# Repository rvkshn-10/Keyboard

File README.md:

# Keyboard 
Hello, this is a Keyboard Project which was my first time developing a PCB, after numerous errors and attempts, I finally got it done thanks to the Half Life Program at Hack Club. 
Firmware for the Raspberry Pi Pico is in the firmware folder, while the PCB and schematic files are in the main folder. Inside of the keyboard61 folder you can find the fabrication files for the circuit board. The layout and pictures have also been put there.

## Bill of materials

This table lists the whole planned build and who is responsible for each purchase. The Hack Club request covers only the rows marked **Hack Club funding request**, the other parts are planned personal purchases. Prices are estimates in USD before checkout unless noted. The PCB estimate is from the older, larger outline and needs a new quote for the compact layout.

| Part | Qty | Unit | Total | Vendor | Buyer |
| --- | ---: | ---: | ---: | --- | --- |
| [Keyboard PCB, batch of 5](https://cart.jlcpcb.com/quote) | 1 | $31.15 | $31.15 | JLCPCB | Hack Club funding request; re-quote revised board |
| [onsemi 1N4148 DO-35 diodes](https://www.digikey.com/en/products/detail/onsemi/1N4148/458603) | 61 | $0.0422 | $2.57 | DigiKey | Hack Club funding request |
| [Raspberry Pi Pico H](https://www.digikey.com/en/products/detail/raspberry-pi/SC0917/16608257) | 1 | $5.00 | $5.00 | DigiKey | Hack Club funding request |
| [Adafruit Pico female socket pair](https://www.digikey.com/en/products/detail/adafruit-industries-llc/5583/16688063) | 1 pair | $0.95 | $0.95 | DigiKey | Hack Club funding request |
| [Adafruit 4111 USB-A to Micro-B cable, 1 m](https://www.digikey.com/en/products/detail/adafruit-industries-llc/4111/9992197) | 1 | $3.95 | $3.95 | DigiKey | Hack Club funding request |
| **Hack Club request parts subtotal** |  |  | **$43.62** |  |  |
| Tax and shipping estimate (not a current checkout quote) | 1 | $20.00 | $20.00 | Multiple vendors | Hack Club request estimate |
| **Estimated Hack Club total** |  |  | **$63.62 of $65** |  | **$1.38 remaining; confirm current carts** |
| [Gateron Milky Yellow Pro V2, 70 switches](https://www.amazon.com/dp/B0BBPPP7HD) | 1 pack | $19.99 | $19.99 | Amazon | Personal purchase |
| [XVX green keycap set](https://www.amazon.com/dp/B0DNMV32L2) | 1 set | $13.99 | $13.99 | Amazon | Personal purchase |
| [Chilkey snap-in stabilizer kit](https://www.amazon.com/dp/B0D2KMVVL3) | 1 kit | $21.99 | $21.99 | Amazon | Personal purchase |
| [Tactile reset buttons, 126-piece pack](https://www.amazon.com/dp/B0D5M2ZNSL) | 1 pack | $4.66 | $4.66 | Amazon | Personal purchase |
| [M3 nylon standoff and fastener kit](https://www.amazon.com/dp/B0G3XCGSNV) | 1 kit | $6.99 | $6.99 | Amazon | Personal purchase |
| [Adafruit rotary encoder with knob](https://www.adafruit.com/product/377) | 1 | $4.50 | $4.50 | Adafruit | Personal purchase |
| [Adafruit 1955 jumper wire pack](https://www.adafruit.com/product/1955) | 1 pack | $3.95 | $3.95 | Adafruit | Personal purchase |
| [ShillehTek AA317 2.8-inch ILI9341 TFT](https://shillehtek.com/products/2-8-spi-tft-lcd-touch-screen-module-240x320-ili9341-for-arduino) | 1 | $10.99 | $10.99 | ShillehTek | Personal purchase |
| Paid printing service for case, plate, and spacers | 1 | Quote needed | Quote needed | TBD | Personal purchase; quote current CAD |
| **Personal parts subtotal** |  |  | **$87.06** |  | **Before tax, shipping, and printing** |
| **Combined known parts subtotal** |  |  | **$130.68** |  | **Before tax, shipping, and printing** |

The $20 tax-and-shipping amount is a planning placeholder, not a confirmed cart total. The Amazon prices were last checked October 7, 2026 and need checkout verification. The prior enclosure-print quote used older geometry and is not included.

## Compact PCB layout

The current KiCad board outline is 295.05 × 100.05 mm, reduced from the earlier 295 × 168 mm layout. The Pico is mounted on the underside beneath the left key area, so it does not need a separate blank strip above the keyboard. Moving it beside the full-width key matrix would require a wider board or a separate wired module, so the current compact outline keeps it inside the keyboard footprint. The two KiCad 3D renders below show the front and underside, physical clearance still needs a hardware fit check.

Here are some images of my work!

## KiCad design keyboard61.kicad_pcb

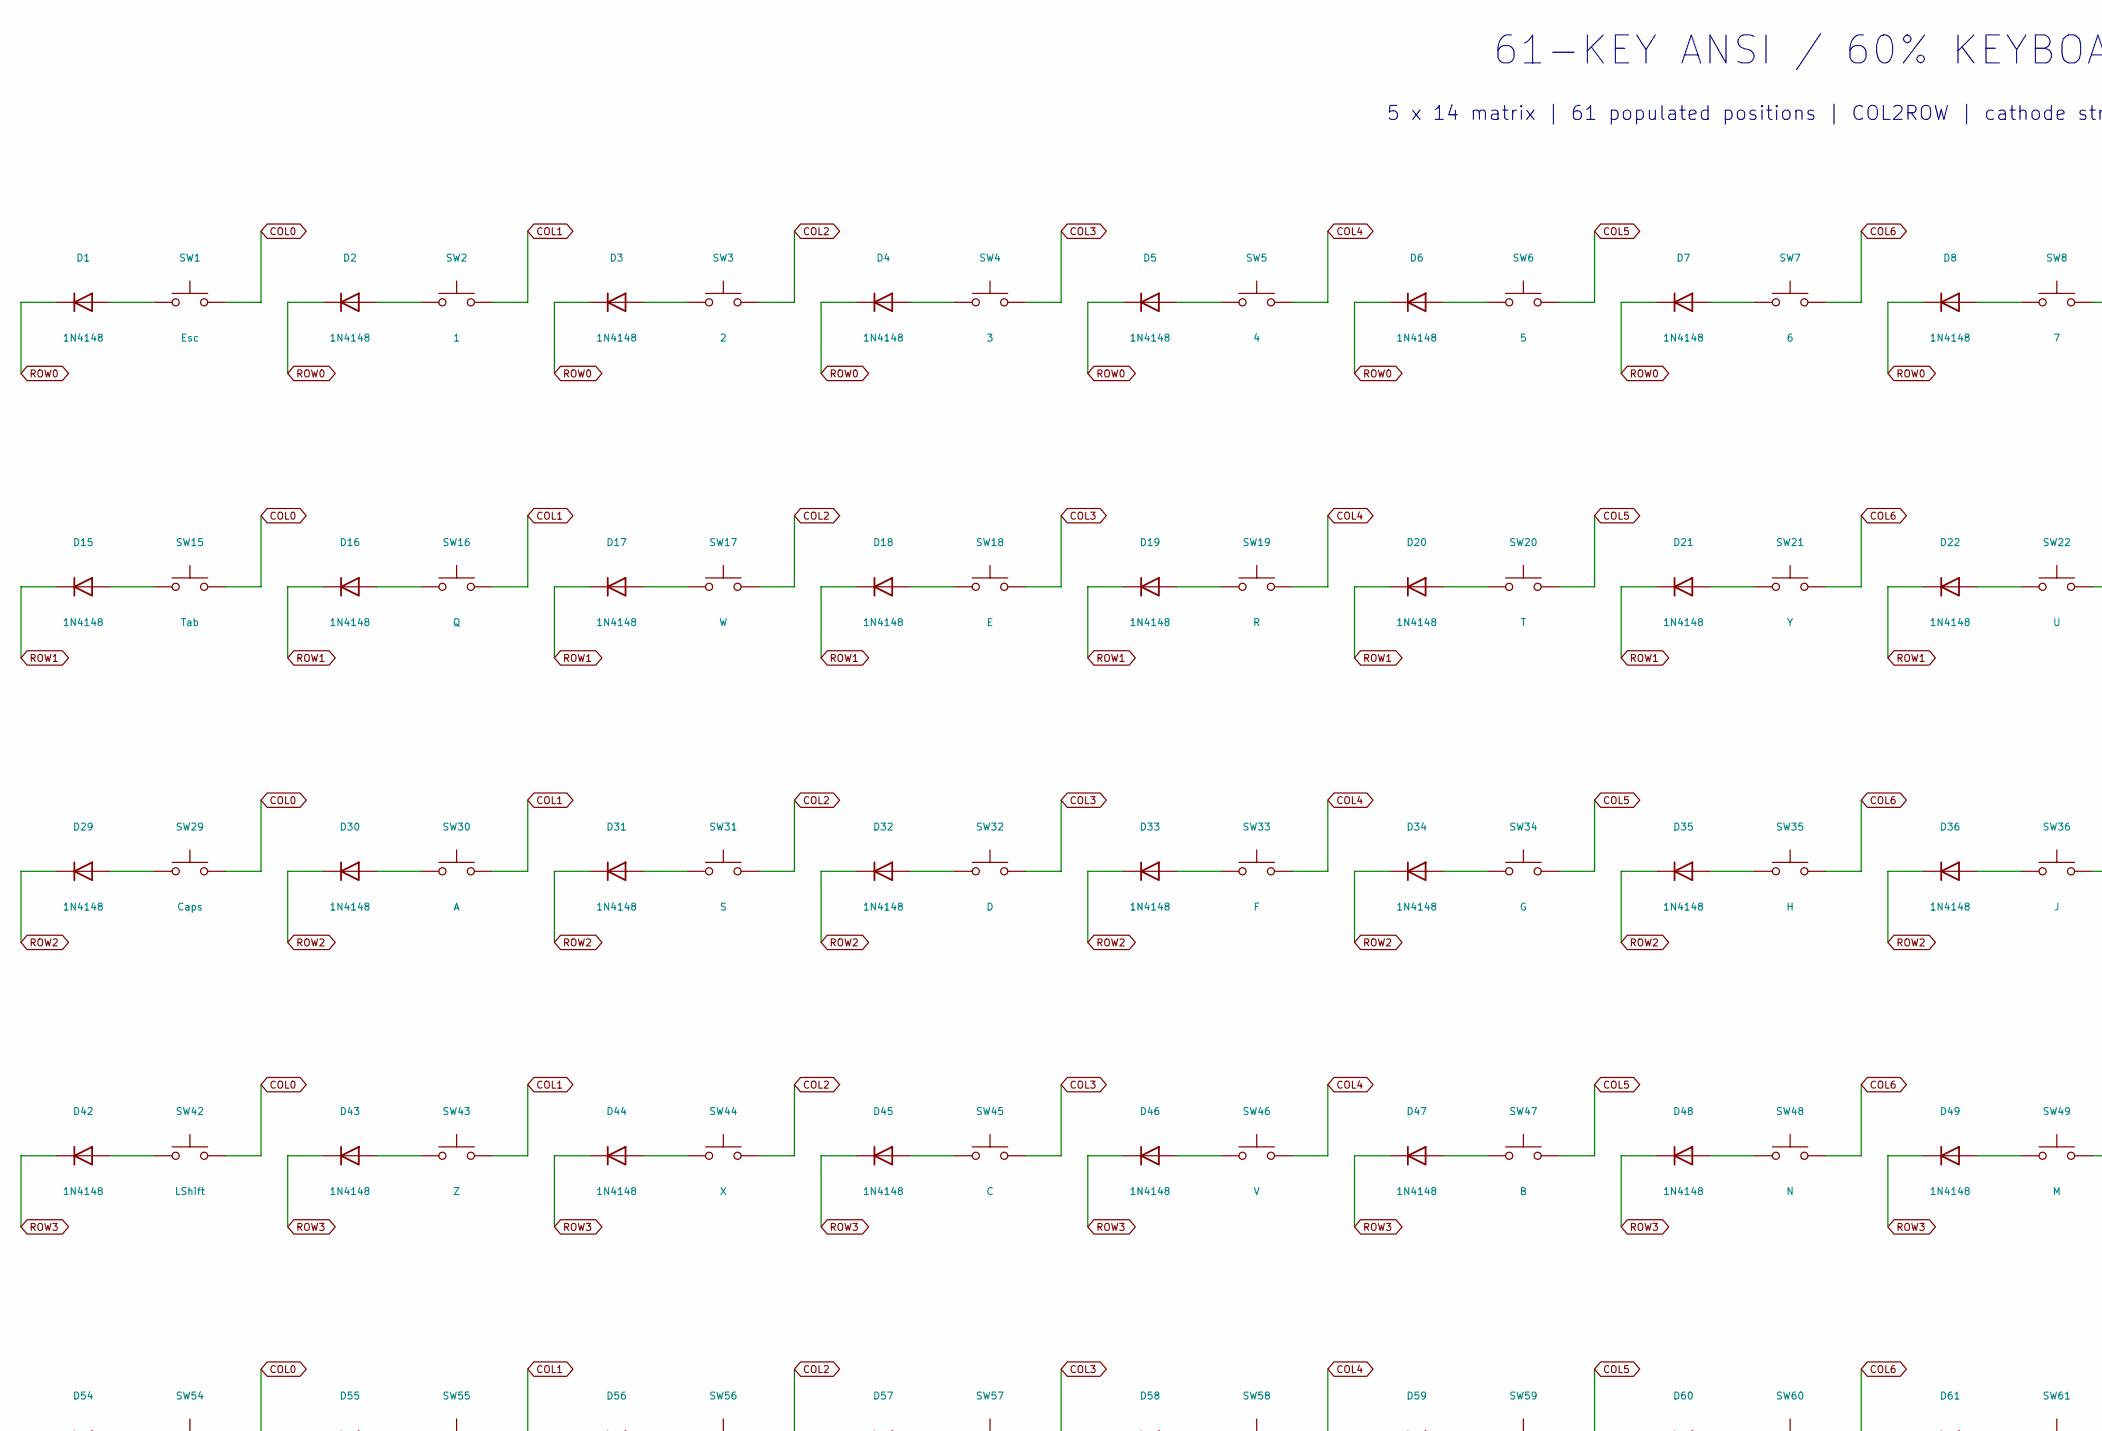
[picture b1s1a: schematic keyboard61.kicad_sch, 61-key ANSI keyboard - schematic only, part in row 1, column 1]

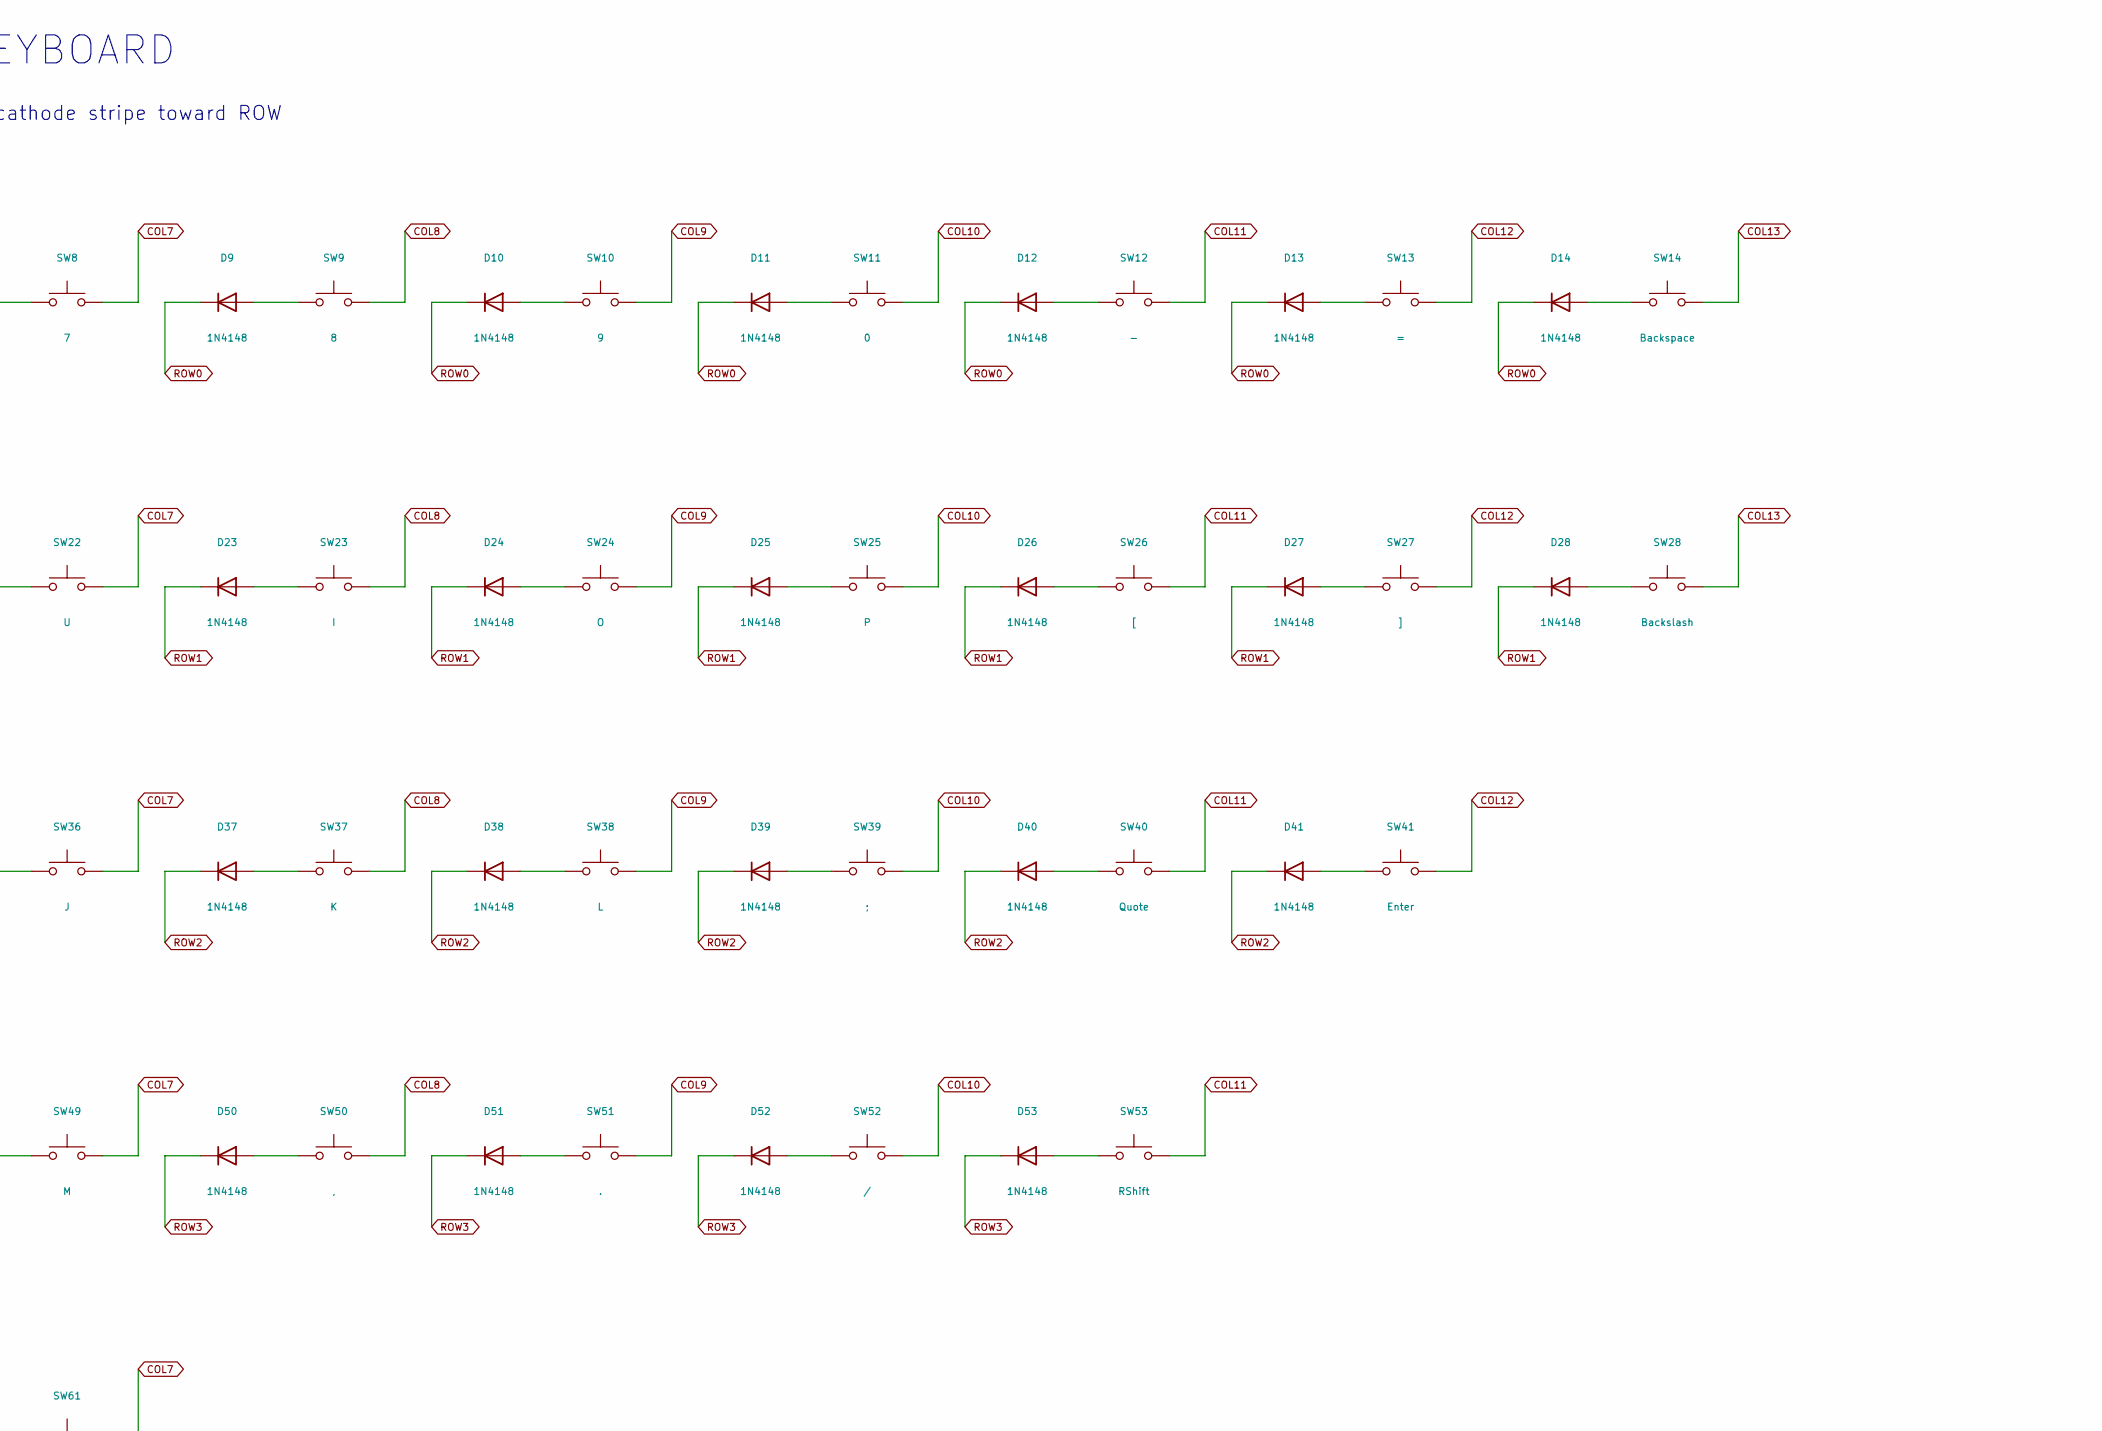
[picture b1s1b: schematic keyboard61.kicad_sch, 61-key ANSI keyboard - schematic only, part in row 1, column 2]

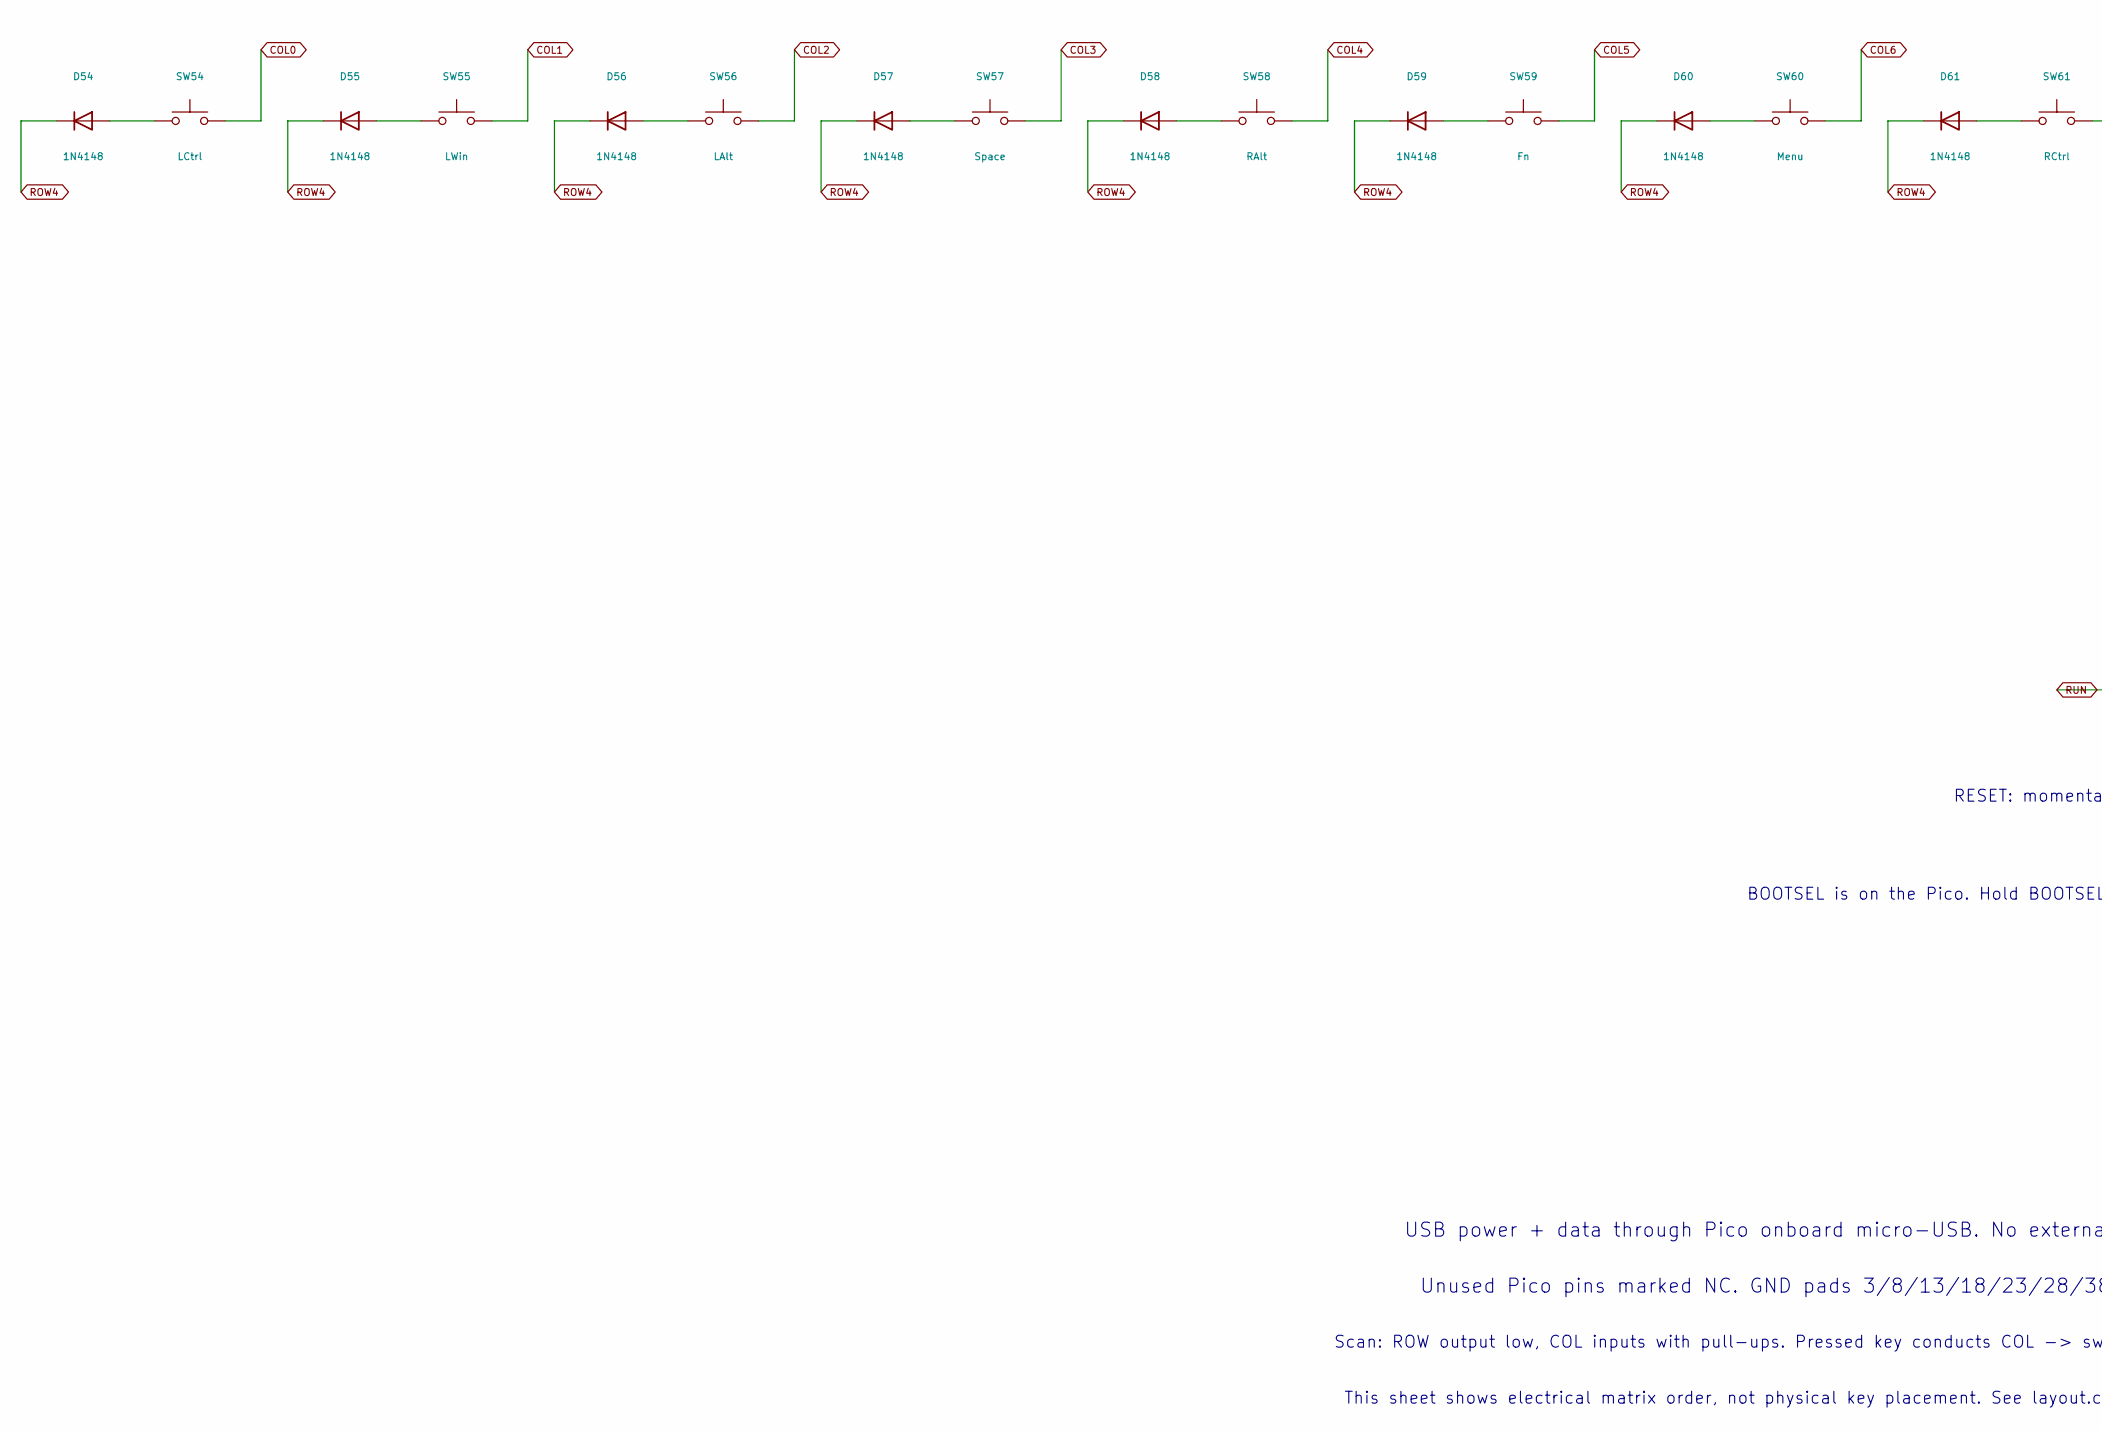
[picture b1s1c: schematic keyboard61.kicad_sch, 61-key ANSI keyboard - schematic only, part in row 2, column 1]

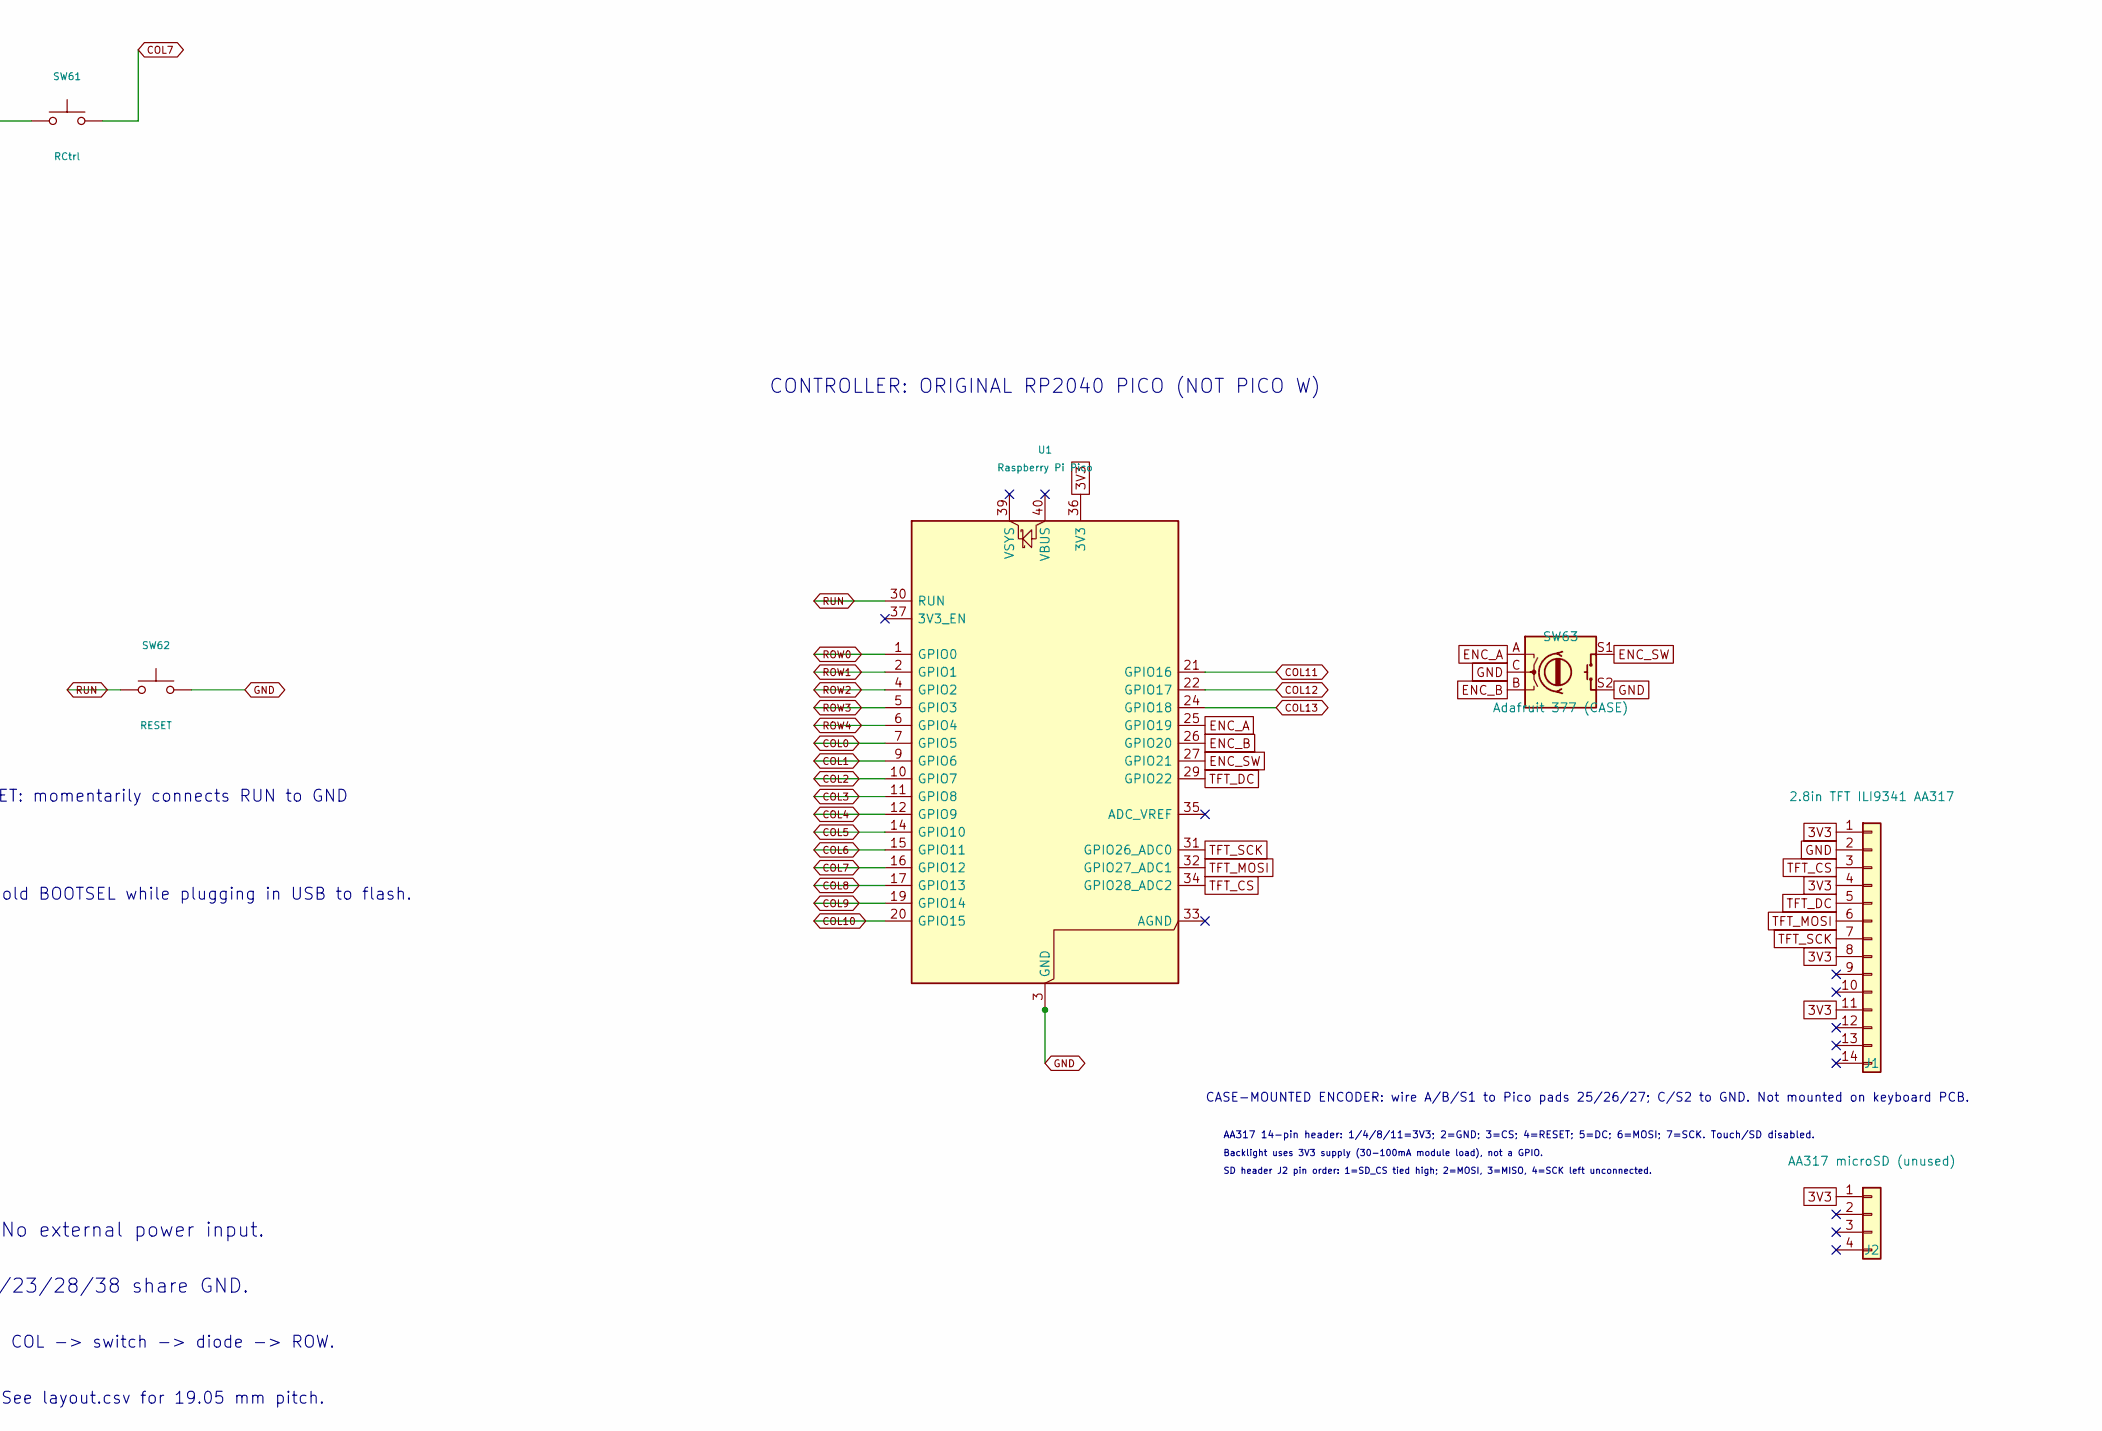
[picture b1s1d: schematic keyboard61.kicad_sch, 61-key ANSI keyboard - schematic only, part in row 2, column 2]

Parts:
D1, D2, D3, D4, D5, D6, D7, D8, D9, D10, D11, D12, D13, D14, D15, D16, D17, D18, D19, D20, D21, D22, D23, D24, D25, D26, D27, D28, D29, D30, D31, D32, D33, D34, D35, D36, D37, D38, D39, D40, D41, D42, D43, D44, D45, D46, D47, D48, D49, D50, D51, D52, D53, D54, D55, D56, D57, D58, D59, D60, D61: 1N4148; D_DO-35_SOD27_P7.62mm_Horizontal
J1: 2.8in TFT ILI9341 AA317
J2: AA317 microSD (unused)
SW1: Esc; SW_Cherry_MX_1.00u_PCB
SW2: 1; SW_Cherry_MX_1.00u_PCB
SW3: 2; SW_Cherry_MX_1.00u_PCB
SW4: 3; SW_Cherry_MX_1.00u_PCB
SW5: 4; SW_Cherry_MX_1.00u_PCB
SW6: 5; SW_Cherry_MX_1.00u_PCB
SW7: 6; SW_Cherry_MX_1.00u_PCB
SW8: 7; SW_Cherry_MX_1.00u_PCB
SW9: 8; SW_Cherry_MX_1.00u_PCB
SW10: 9; SW_Cherry_MX_1.00u_PCB
SW11: 0; SW_Cherry_MX_1.00u_PCB
SW12: -; SW_Cherry_MX_1.00u_PCB
SW13: =; SW_Cherry_MX_1.00u_PCB
SW14: Backspace; SW_Cherry_MX_2.00u_PCB
SW15: Tab; SW_Cherry_MX_1.50u_PCB_SocketClearance
SW16: Q; SW_Cherry_MX_1.00u_PCB_SocketClearance
SW17: W; SW_Cherry_MX_1.00u_PCB
SW18: E; SW_Cherry_MX_1.00u_PCB
SW19: R; SW_Cherry_MX_1.00u_PCB
SW20: T; SW_Cherry_MX_1.00u_PCB
SW21: Y; SW_Cherry_MX_1.00u_PCB
SW22: U; SW_Cherry_MX_1.00u_PCB
SW23: I; SW_Cherry_MX_1.00u_PCB
SW24: O; SW_Cherry_MX_1.00u_PCB
SW25: P; SW_Cherry_MX_1.00u_PCB
SW26: [; SW_Cherry_MX_1.00u_PCB
SW27: ]; SW_Cherry_MX_1.00u_PCB
SW28: Backslash; SW_Cherry_MX_1.50u_PCB
SW29: Caps; SW_Cherry_MX_1.75u_PCB
SW30: A; SW_Cherry_MX_1.00u_PCB
SW31: S; SW_Cherry_MX_1.00u_PCB
SW32: D; SW_Cherry_MX_1.00u_PCB
SW33: F; SW_Cherry_MX_1.00u_PCB
SW34: G; SW_Cherry_MX_1.00u_PCB
SW35: H; SW_Cherry_MX_1.00u_PCB
SW36: J; SW_Cherry_MX_1.00u_PCB
SW37: K; SW_Cherry_MX_1.00u_PCB
SW38: L; SW_Cherry_MX_1.00u_PCB
SW39: ;; SW_Cherry_MX_1.00u_PCB
SW40: Quote; SW_Cherry_MX_1.00u_PCB
SW41: Enter; SW_Cherry_MX_2.25u_PCB
SW42: LShift; SW_Cherry_MX_2.25u_PCB
SW43: Z; SW_Cherry_MX_1.00u_PCB
SW44: X; SW_Cherry_MX_1.00u_PCB
SW45: C; SW_Cherry_MX_1.00u_PCB
SW46: V; SW_Cherry_MX_1.00u_PCB
SW47: B; SW_Cherry_MX_1.00u_PCB
SW48: N; SW_Cherry_MX_1.00u_PCB
SW49: M; SW_Cherry_MX_1.00u_PCB
SW50: ,; SW_Cherry_MX_1.00u_PCB
SW51: .; SW_Cherry_MX_1.00u_PCB
SW52: /; SW_Cherry_MX_1.00u_PCB
SW53: RShift; SW_Cherry_MX_2.75u_PCB
SW54: LCtrl; SW_Cherry_MX_1.25u_PCB
SW55: LWin; SW_Cherry_MX_1.25u_PCB
SW56: LAlt; SW_Cherry_MX_1.25u_PCB
SW57: Space; SW_Cherry_MX_6.25u_PCB
SW58: RAlt; SW_Cherry_MX_1.25u_PCB
SW59: Fn; SW_Cherry_MX_1.25u_PCB
SW60: Menu; SW_Cherry_MX_1.25u_PCB
SW61: RCtrl; SW_Cherry_MX_1.25u_PCB
SW62: RESET; SW_PUSH_6mm
SW63: Adafruit 377 (CASE)
U1: Raspberry Pi Pico; Pico_H_Bottom_Sockets_8_5mm

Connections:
3V3: J1.1, J1.4, J1.8, J1.11, J2.1, U1.36 (3V3)
COL0: SW1.2, SW15.2, SW29.2, SW42.2, SW54.2, U1.7 (GPIO5)
COL1: SW2.2, SW16.2, SW30.2, SW43.2, SW55.2, U1.9 (GPIO6)
COL2: SW3.2, SW17.2, SW31.2, SW44.2, SW56.2, U1.10 (GPIO7)
COL3: SW4.2, SW18.2, SW32.2, SW45.2, SW57.2, U1.11 (GPIO8)
COL4: SW5.2, SW19.2, SW33.2, SW46.2, SW58.2, U1.12 (GPIO9)
COL5: SW6.2, SW20.2, SW34.2, SW47.2, SW59.2, U1.14 (GPIO10)
COL6: SW7.2, SW21.2, SW35.2, SW48.2, SW60.2, U1.15 (GPIO11)
COL7: SW8.2, SW22.2, SW36.2, SW49.2, SW61.2, U1.16 (GPIO12)
COL8: SW9.2, SW23.2, SW37.2, SW50.2, U1.17 (GPIO13)
COL9: SW10.2, SW24.2, SW38.2, SW51.2, U1.19 (GPIO14)
COL10: SW11.2, SW25.2, SW39.2, SW52.2, U1.20 (GPIO15)
COL11: SW12.2, SW26.2, SW40.2, SW53.2, U1.21 (GPIO16)
COL12: SW13.2, SW27.2, SW41.2, U1.22 (GPIO17)
COL13: SW14.2, SW28.2, U1.24 (GPIO18)
ENC_A: SW63.A, U1.25 (GPIO19)
ENC_B: SW63.B, U1.26 (GPIO20)
ENC_SW: SW63.S1, U1.27 (GPIO21)
GND: J1.2, SW62.2, SW63.C, SW63.S2, U1.3 (GND), U1.8 (GND), U1.13 (GND), U1.18 (GND), U1.23 (GND), U1.28 (GND), U1.38 (GND)
unnamed: D1.2 (A), SW1.1
unnamed: D2.2 (A), SW2.1
unnamed: D3.2 (A), SW3.1
unnamed: D4.2 (A), SW4.1
unnamed: D5.2 (A), SW5.1
unnamed: D6.2 (A), SW6.1
unnamed: D7.2 (A), SW7.1
unnamed: D8.2 (A), SW8.1
unnamed: D9.2 (A), SW9.1
unnamed: D10.2 (A), SW10.1
unnamed: D11.2 (A), SW11.1
unnamed: D12.2 (A), SW12.1
unnamed: D13.2 (A), SW13.1
unnamed: D14.2 (A), SW14.1
unnamed: D15.2 (A), SW15.1
unnamed: D16.2 (A), SW16.1
unnamed: D17.2 (A), SW17.1
unnamed: D18.2 (A), SW18.1
unnamed: D19.2 (A), SW19.1
unnamed: D20.2 (A), SW20.1
unnamed: D21.2 (A), SW21.1
unnamed: D22.2 (A), SW22.1
unnamed: D23.2 (A), SW23.1
unnamed: D24.2 (A), SW24.1
unnamed: D25.2 (A), SW25.1
unnamed: D26.2 (A), SW26.1
unnamed: D27.2 (A), SW27.1
unnamed: D28.2 (A), SW28.1
unnamed: D29.2 (A), SW29.1
unnamed: D30.2 (A), SW30.1
unnamed: D31.2 (A), SW31.1
unnamed: D32.2 (A), SW32.1
unnamed: D33.2 (A), SW33.1
unnamed: D34.2 (A), SW34.1
unnamed: D35.2 (A), SW35.1
unnamed: D36.2 (A), SW36.1
unnamed: D37.2 (A), SW37.1
unnamed: D38.2 (A), SW38.1
unnamed: D39.2 (A), SW39.1
unnamed: D40.2 (A), SW40.1
unnamed: D41.2 (A), SW41.1
unnamed: D42.2 (A), SW42.1
unnamed: D43.2 (A), SW43.1
unnamed: D44.2 (A), SW44.1
unnamed: D45.2 (A), SW45.1
unnamed: D46.2 (A), SW46.1
unnamed: D47.2 (A), SW47.1
unnamed: D48.2 (A), SW48.1
unnamed: D49.2 (A), SW49.1
unnamed: D50.2 (A), SW50.1
unnamed: D51.2 (A), SW51.1
unnamed: D52.2 (A), SW52.1
unnamed: D53.2 (A), SW53.1
unnamed: D54.2 (A), SW54.1
unnamed: D55.2 (A), SW55.1
unnamed: D56.2 (A), SW56.1
unnamed: D57.2 (A), SW57.1
unnamed: D58.2 (A), SW58.1
unnamed: D59.2 (A), SW59.1
unnamed: D60.2 (A), SW60.1
unnamed: D61.2 (A), SW61.1
ROW0: D1.1 (K), D2.1 (K), D3.1 (K), D4.1 (K), D5.1 (K), D6.1 (K), D7.1 (K), D8.1 (K), D9.1 (K), D10.1 (K), D11.1 (K), D12.1 (K), D13.1 (K), D14.1 (K), U1.1 (GPIO0)
ROW1: D15.1 (K), D16.1 (K), D17.1 (K), D18.1 (K), D19.1 (K), D20.1 (K), D21.1 (K), D22.1 (K), D23.1 (K), D24.1 (K), D25.1 (K), D26.1 (K), D27.1 (K), D28.1 (K), U1.2 (GPIO1)
ROW2: D29.1 (K), D30.1 (K), D31.1 (K), D32.1 (K), D33.1 (K), D34.1 (K), D35.1 (K), D36.1 (K), D37.1 (K), D38.1 (K), D39.1 (K), D40.1 (K), D41.1 (K), U1.4 (GPIO2)
ROW3: D42.1 (K), D43.1 (K), D44.1 (K), D45.1 (K), D46.1 (K), D47.1 (K), D48.1 (K), D49.1 (K), D50.1 (K), D51.1 (K), D52.1 (K), D53.1 (K), U1.5 (GPIO3)
ROW4: D54.1 (K), D55.1 (K), D56.1 (K), D57.1 (K), D58.1 (K), D59.1 (K), D60.1 (K), D61.1 (K), U1.6 (GPIO4)
RUN: SW62.1, U1.30 (RUN)
TFT_CS: J1.3, U1.34 (GPIO28_ADC2)
TFT_DC: J1.5, U1.29 (GPIO22)
TFT_MOSI: J1.6, U1.32 (GPIO27_ADC1)
TFT_SCK: J1.7, U1.31 (GPIO26_ADC0)

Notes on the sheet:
USB power + data through Pico onboard micro-USB. No external power input.
Unused Pico pins marked NC. GND pads 3/8/13/18/23/28/38 share GND.
61-KEY ANSI / 60% KEYBOARD
Scan: ROW output low, COL inputs with pull-ups. Pressed key conducts COL -> switch -> diode -> ROW.
BOOTSEL is on the Pico. Hold BOOTSEL while plugging in USB to flash.
5 x 14 matrix | 61 populated positions | COL2ROW | cathode stripe toward ROW
RESET: momentarily connects RUN to GND
CONTROLLER: ORIGINAL RP2040 PICO (NOT PICO W)
This sheet shows electrical matrix order, not physical key placement. See layout.csv for 19.05 mm pitch.
AA317 14-pin header: 1/4/8/11=3V3; 2=GND; 3=CS; 4=RESET; 5=DC; 6=MOSI; 7=SCK. Touch/SD disabled.
Backlight uses 3V3 supply (30-100mA module load), not a GPIO.
SD header J2 pin order: 1=SD_CS tied high; 2=MOSI, 3=MISO, 4=SCK left unconnected.
CASE-MOUNTED ENCODER: wire A/B/S1 to Pico pads 25/26/27; C/S2 to GND. Not mounted on keyboard PCB.

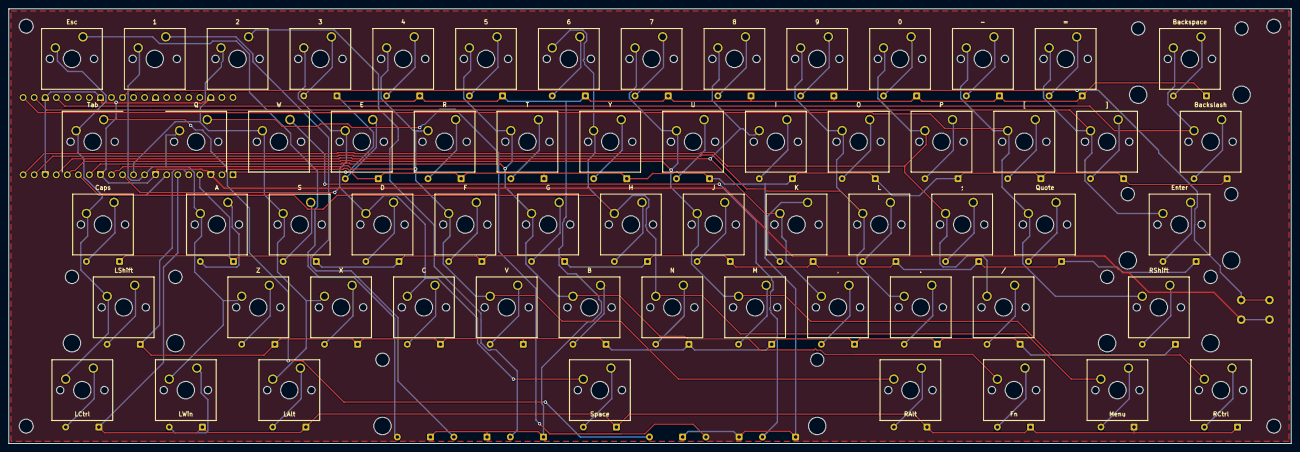
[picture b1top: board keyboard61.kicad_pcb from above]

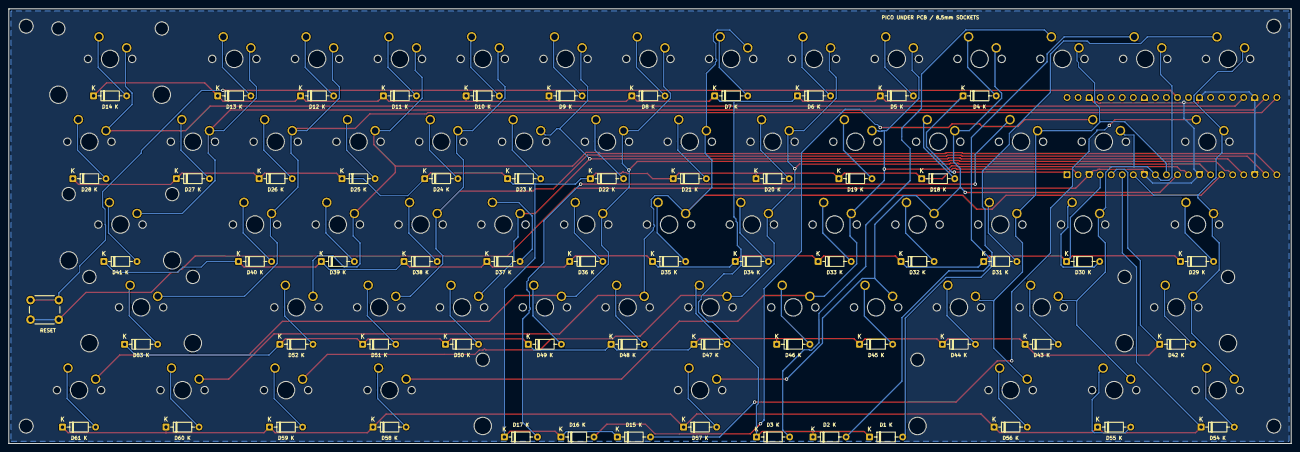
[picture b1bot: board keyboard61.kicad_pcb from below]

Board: 2 copper layers, 295.0 x 100.0 mm, 128 parts (63 on the bottom side), 82 nets.

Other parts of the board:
H1, H2, H3, H4: MountingHole_3.2mm_M3

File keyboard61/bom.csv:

Reference,Value,Footprint
D1,1N4148,Diode_THT:D_DO-35_SOD27_P7.62mm_Horizontal
D2,1N4148,Diode_THT:D_DO-35_SOD27_P7.62mm_Horizontal
D3,1N4148,Diode_THT:D_DO-35_SOD27_P7.62mm_Horizontal
D4,1N4148,Diode_THT:D_DO-35_SOD27_P7.62mm_Horizontal
D5,1N4148,Diode_THT:D_DO-35_SOD27_P7.62mm_Horizontal
D6,1N4148,Diode_THT:D_DO-35_SOD27_P7.62mm_Horizontal
D7,1N4148,Diode_THT:D_DO-35_SOD27_P7.62mm_Horizontal
D8,1N4148,Diode_THT:D_DO-35_SOD27_P7.62mm_Horizontal
D9,1N4148,Diode_THT:D_DO-35_SOD27_P7.62mm_Horizontal
D10,1N4148,Diode_THT:D_DO-35_SOD27_P7.62mm_Horizontal
D11,1N4148,Diode_THT:D_DO-35_SOD27_P7.62mm_Horizontal
D12,1N4148,Diode_THT:D_DO-35_SOD27_P7.62mm_Horizontal
D13,1N4148,Diode_THT:D_DO-35_SOD27_P7.62mm_Horizontal
D14,1N4148,Diode_THT:D_DO-35_SOD27_P7.62mm_Horizontal
D15,1N4148,Diode_THT:D_DO-35_SOD27_P7.62mm_Horizontal
D16,1N4148,Diode_THT:D_DO-35_SOD27_P7.62mm_Horizontal
D17,1N4148,Diode_THT:D_DO-35_SOD27_P7.62mm_Horizontal
D18,1N4148,Diode_THT:D_DO-35_SOD27_P7.62mm_Horizontal
D19,1N4148,Diode_THT:D_DO-35_SOD27_P7.62mm_Horizontal
D20,1N4148,Diode_THT:D_DO-35_SOD27_P7.62mm_Horizontal
D21,1N4148,Diode_THT:D_DO-35_SOD27_P7.62mm_Horizontal
D22,1N4148,Diode_THT:D_DO-35_SOD27_P7.62mm_Horizontal
D23,1N4148,Diode_THT:D_DO-35_SOD27_P7.62mm_Horizontal
D24,1N4148,Diode_THT:D_DO-35_SOD27_P7.62mm_Horizontal
D25,1N4148,Diode_THT:D_DO-35_SOD27_P7.62mm_Horizontal
D26,1N4148,Diode_THT:D_DO-35_SOD27_P7.62mm_Horizontal
D27,1N4148,Diode_THT:D_DO-35_SOD27_P7.62mm_Horizontal
D28,1N4148,Diode_THT:D_DO-35_SOD27_P7.62mm_Horizontal
D29,1N4148,Diode_THT:D_DO-35_SOD27_P7.62mm_Horizontal
D30,1N4148,Diode_THT:D_DO-35_SOD27_P7.62mm_Horizontal
D31,1N4148,Diode_THT:D_DO-35_SOD27_P7.62mm_Horizontal
D32,1N4148,Diode_THT:D_DO-35_SOD27_P7.62mm_Horizontal
D33,1N4148,Diode_THT:D_DO-35_SOD27_P7.62mm_Horizontal
D34,1N4148,Diode_THT:D_DO-35_SOD27_P7.62mm_Horizontal
D35,1N4148,Diode_THT:D_DO-35_SOD27_P7.62mm_Horizontal
D36,1N4148,Diode_THT:D_DO-35_SOD27_P7.62mm_Horizontal
D37,1N4148,Diode_THT:D_DO-35_SOD27_P7.62mm_Horizontal
D38,1N4148,Diode_THT:D_DO-35_SOD27_P7.62mm_Horizontal
D39,1N4148,Diode_THT:D_DO-35_SOD27_P7.62mm_Horizontal
D40,1N4148,Diode_THT:D_DO-35_SOD27_P7.62mm_Horizontal
D41,1N4148,Diode_THT:D_DO-35_SOD27_P7.62mm_Horizontal
D42,1N4148,Diode_THT:D_DO-35_SOD27_P7.62mm_Horizontal
D43,1N4148,Diode_THT:D_DO-35_SOD27_P7.62mm_Horizontal
D44,1N4148,Diode_THT:D_DO-35_SOD27_P7.62mm_Horizontal
D45,1N4148,Diode_THT:D_DO-35_SOD27_P7.62mm_Horizontal
D46,1N4148,Diode_THT:D_DO-35_SOD27_P7.62mm_Horizontal
D47,1N4148,Diode_THT:D_DO-35_SOD27_P7.62mm_Horizontal
D48,1N4148,Diode_THT:D_DO-35_SOD27_P7.62mm_Horizontal
D49,1N4148,Diode_THT:D_DO-35_SOD27_P7.62mm_Horizontal
D50,1N4148,Diode_THT:D_DO-35_SOD27_P7.62mm_Horizontal
D51,1N4148,Diode_THT:D_DO-35_SOD27_P7.62mm_Horizontal
D52,1N4148,Diode_THT:D_DO-35_SOD27_P7.62mm_Horizontal
D53,1N4148,Diode_THT:D_DO-35_SOD27_P7.62mm_Horizontal
D54,1N4148,Diode_THT:D_DO-35_SOD27_P7.62mm_Horizontal
D55,1N4148,Diode_THT:D_DO-35_SOD27_P7.62mm_Horizontal
D56,1N4148,Diode_THT:D_DO-35_SOD27_P7.62mm_Horizontal
D57,1N4148,Diode_THT:D_DO-35_SOD27_P7.62mm_Horizontal
D58,1N4148,Diode_THT:D_DO-35_SOD27_P7.62mm_Horizontal
D59,1N4148,Diode_THT:D_DO-35_SOD27_P7.62mm_Horizontal
D60,1N4148,Diode_THT:D_DO-35_SOD27_P7.62mm_Horizontal
D61,1N4148,Diode_THT:D_DO-35_SOD27_P7.62mm_Horizontal
SW1,Esc,Button_Switch_Keyboard:SW_Cherry_MX_1.00u_PCB
SW2,1,Button_Switch_Keyboard:SW_Cherry_MX_1.00u_PCB
SW3,2,Button_Switch_Keyboard:SW_Cherry_MX_1.00u_PCB
SW4,3,Button_Switch_Keyboard:SW_Cherry_MX_1.00u_PCB
SW5,4,Button_Switch_Keyboard:SW_Cherry_MX_1.00u_PCB
SW6,5,Button_Switch_Keyboard:SW_Cherry_MX_1.00u_PCB
SW7,6,Button_Switch_Keyboard:SW_Cherry_MX_1.00u_PCB
SW8,7,Button_Switch_Keyboard:SW_Cherry_MX_1.00u_PCB
SW9,8,Button_Switch_Keyboard:SW_Cherry_MX_1.00u_PCB
SW10,9,Button_Switch_Keyboard:SW_Cherry_MX_1.00u_PCB
SW11,0,Button_Switch_Keyboard:SW_Cherry_MX_1.00u_PCB
SW12,-,Button_Switch_Keyboard:SW_Cherry_MX_1.00u_PCB
SW13,=,Button_Switch_Keyboard:SW_Cherry_MX_1.00u_PCB
SW14,Backspace,Button_Switch_Keyboard:SW_Cherry_MX_2.00u_PCB
SW15,Tab,Button_Switch_Keyboard:SW_Cherry_MX_1.50u_PCB
SW16,Q,Button_Switch_Keyboard:SW_Cherry_MX_1.00u_PCB
SW17,W,Button_Switch_Keyboard:SW_Cherry_MX_1.00u_PCB
SW18,E,Button_Switch_Keyboard:SW_Cherry_MX_1.00u_PCB
SW19,R,Button_Switch_Keyboard:SW_Cherry_MX_1.00u_PCB
SW20,T,Button_Switch_Keyboard:SW_Cherry_MX_1.00u_PCB
SW21,Y,Button_Switch_Keyboard:SW_Cherry_MX_1.00u_PCB
SW22,U,Button_Switch_Keyboard:SW_Cherry_MX_1.00u_PCB
SW23,I,Button_Switch_Keyboard:SW_Cherry_MX_1.00u_PCB
SW24,O,Button_Switch_Keyboard:SW_Cherry_MX_1.00u_PCB
SW25,P,Button_Switch_Keyboard:SW_Cherry_MX_1.00u_PCB
SW26,[,Button_Switch_Keyboard:SW_Cherry_MX_1.00u_PCB
SW27,],Button_Switch_Keyboard:SW_Cherry_MX_1.00u_PCB
SW28,Backslash,Button_Switch_Keyboard:SW_Cherry_MX_1.50u_PCB
SW29,Caps,Button_Switch_Keyboard:SW_Cherry_MX_1.75u_PCB
SW30,A,Button_Switch_Keyboard:SW_Cherry_MX_1.00u_PCB
SW31,S,Button_Switch_Keyboard:SW_Cherry_MX_1.00u_PCB
SW32,D,Button_Switch_Keyboard:SW_Cherry_MX_1.00u_PCB
SW33,F,Button_Switch_Keyboard:SW_Cherry_MX_1.00u_PCB
SW34,G,Button_Switch_Keyboard:SW_Cherry_MX_1.00u_PCB
SW35,H,Button_Switch_Keyboard:SW_Cherry_MX_1.00u_PCB
SW36,J,Button_Switch_Keyboard:SW_Cherry_MX_1.00u_PCB
SW37,K,Button_Switch_Keyboard:SW_Cherry_MX_1.00u_PCB
SW38,L,Button_Switch_Keyboard:SW_Cherry_MX_1.00u_PCB
SW39,;,Button_Switch_Keyboard:SW_Cherry_MX_1.00u_PCB
SW40,Quote,Button_Switch_Keyboard:SW_Cherry_MX_1.00u_PCB
SW41,Enter,Button_Switch_Keyboard:SW_Cherry_MX_2.25u_PCB
SW42,LShift,Button_Switch_Keyboard:SW_Cherry_MX_2.25u_PCB
SW43,Z,Button_Switch_Keyboard:SW_Cherry_MX_1.00u_PCB
SW44,X,Button_Switch_Keyboard:SW_Cherry_MX_1.00u_PCB
SW45,C,Button_Switch_Keyboard:SW_Cherry_MX_1.00u_PCB
SW46,V,Button_Switch_Keyboard:SW_Cherry_MX_1.00u_PCB
SW47,B,Button_Switch_Keyboard:SW_Cherry_MX_1.00u_PCB
SW48,N,Button_Switch_Keyboard:SW_Cherry_MX_1.00u_PCB
SW49,M,Button_Switch_Keyboard:SW_Cherry_MX_1.00u_PCB
SW50,",",Button_Switch_Keyboard:SW_Cherry_MX_1.00u_PCB
SW51,.,Button_Switch_Keyboard:SW_Cherry_MX_1.00u_PCB
SW52,/,Button_Switch_Keyboard:SW_Cherry_MX_1.00u_PCB
SW53,RShift,Button_Switch_Keyboard:SW_Cherry_MX_2.75u_PCB
SW54,LCtrl,Button_Switch_Keyboard:SW_Cherry_MX_1.25u_PCB
SW55,LWin,Button_Switch_Keyboard:SW_Cherry_MX_1.25u_PCB
SW56,LAlt,Button_Switch_Keyboard:SW_Cherry_MX_1.25u_PCB
SW57,Space,Button_Switch_Keyboard:SW_Cherry_MX_6.25u_PCB
SW58,RAlt,Button_Switch_Keyboard:SW_Cherry_MX_1.25u_PCB
SW59,Fn,Button_Switch_Keyboard:SW_Cherry_MX_1.25u_PCB
SW60,Menu,Button_Switch_Keyboard:SW_Cherry_MX_1.25u_PCB
SW61,RCtrl,Button_Switch_Keyboard:SW_Cherry_MX_1.25u_PCB
SW62,RESET,Button_Switch_THT:SW_PUSH_6mm
U1,Raspberry Pi Pico,Module:RaspberryPi_Pico_Common_THT
